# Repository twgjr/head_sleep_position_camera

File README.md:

# Tracking head position while sleeping
In 2017 my new born son had formed a flat spot on his head due to Torticollis (stiff neck that makes it hard or painful to turn your head).  Fortunately, he had successful physical therapy to correct the condition.

That inspired this hobby project as a way to track how long an infant spent sleeping on one part of their head.  At the time (2017) I was a power system engineer for electric utilities.  I had learned some embedded system PCB designand programming in school, but was a little rusty.  It allowed me to explore embedded PCB design and programming and also introduced me to machine learning and AI applications.

As a result of Git not yet being serious part of my life in 2017, very few files were saved other than mentioned below.  I have since then adopted Git to save progress with my software and hardware projects!

## Development
I expermented on two different device concepts:  

1.  Wearable:  A battery powered tile worn as a head band.  It used an accelerometer to track the position of the head.  Though simple and inexpensive, this was quickly abandoned due to risks of choking and batteries near infants.

1.  Camera:  Camera to observe sleeping head pose without contact.  Used head pose detection AI and on-board accelerometer to estimate the head position relative to a flat level bed.  Two approaches were tried for the camera:

    * On-device AI model:  The camera used a Raspberry Pi to run a head pose detection AI model.  The head pose would then be corrected with the accelerometer data to estimate the head position relative to the bed.  I based the proof of concept on the LearnOpenCV blog post [Head Pose Estimation using OpenCV and Dlib](https://www.learnopencv.com/head-pose-estimation-using-opencv-and-dlib/).  This could only process 1 frame per 30 seconds. So, I would need to find a more efficient AI model or a more powerful (expensive) processor.

    * Cloud AI model:  The camera would send an image of the head to AWS Rekognition to calculate the head pose relative to the camera.  The head pose would then be corrected with the accelerometer data to estimate the head position relative to the bed.  This was the most promising approach, and least expensive hardware.  However, the cost of running the AI model on the cloud was too expensive to be practical.  The PCB I designed for this approach is the only work I have saved.  It is in the `hardware` directory.  (requires Fusion 360 to view or edit.)

## Current Status and Future Work
The cost of running the AI to track the head position was too cost prohibitive to be practical for most people at the time.  It would either require a lot of cloud computing resources or much more expensive processing on the device itself.

I have since moved on to other projects, but I would like to revisit this project in the future.  When I do, I would like to explore the following:
*  More efficient AI models (computer vision and machine learning have advanced a lot since 2017)
*  More efficient processing on the device (newer processors with AI acceleration)

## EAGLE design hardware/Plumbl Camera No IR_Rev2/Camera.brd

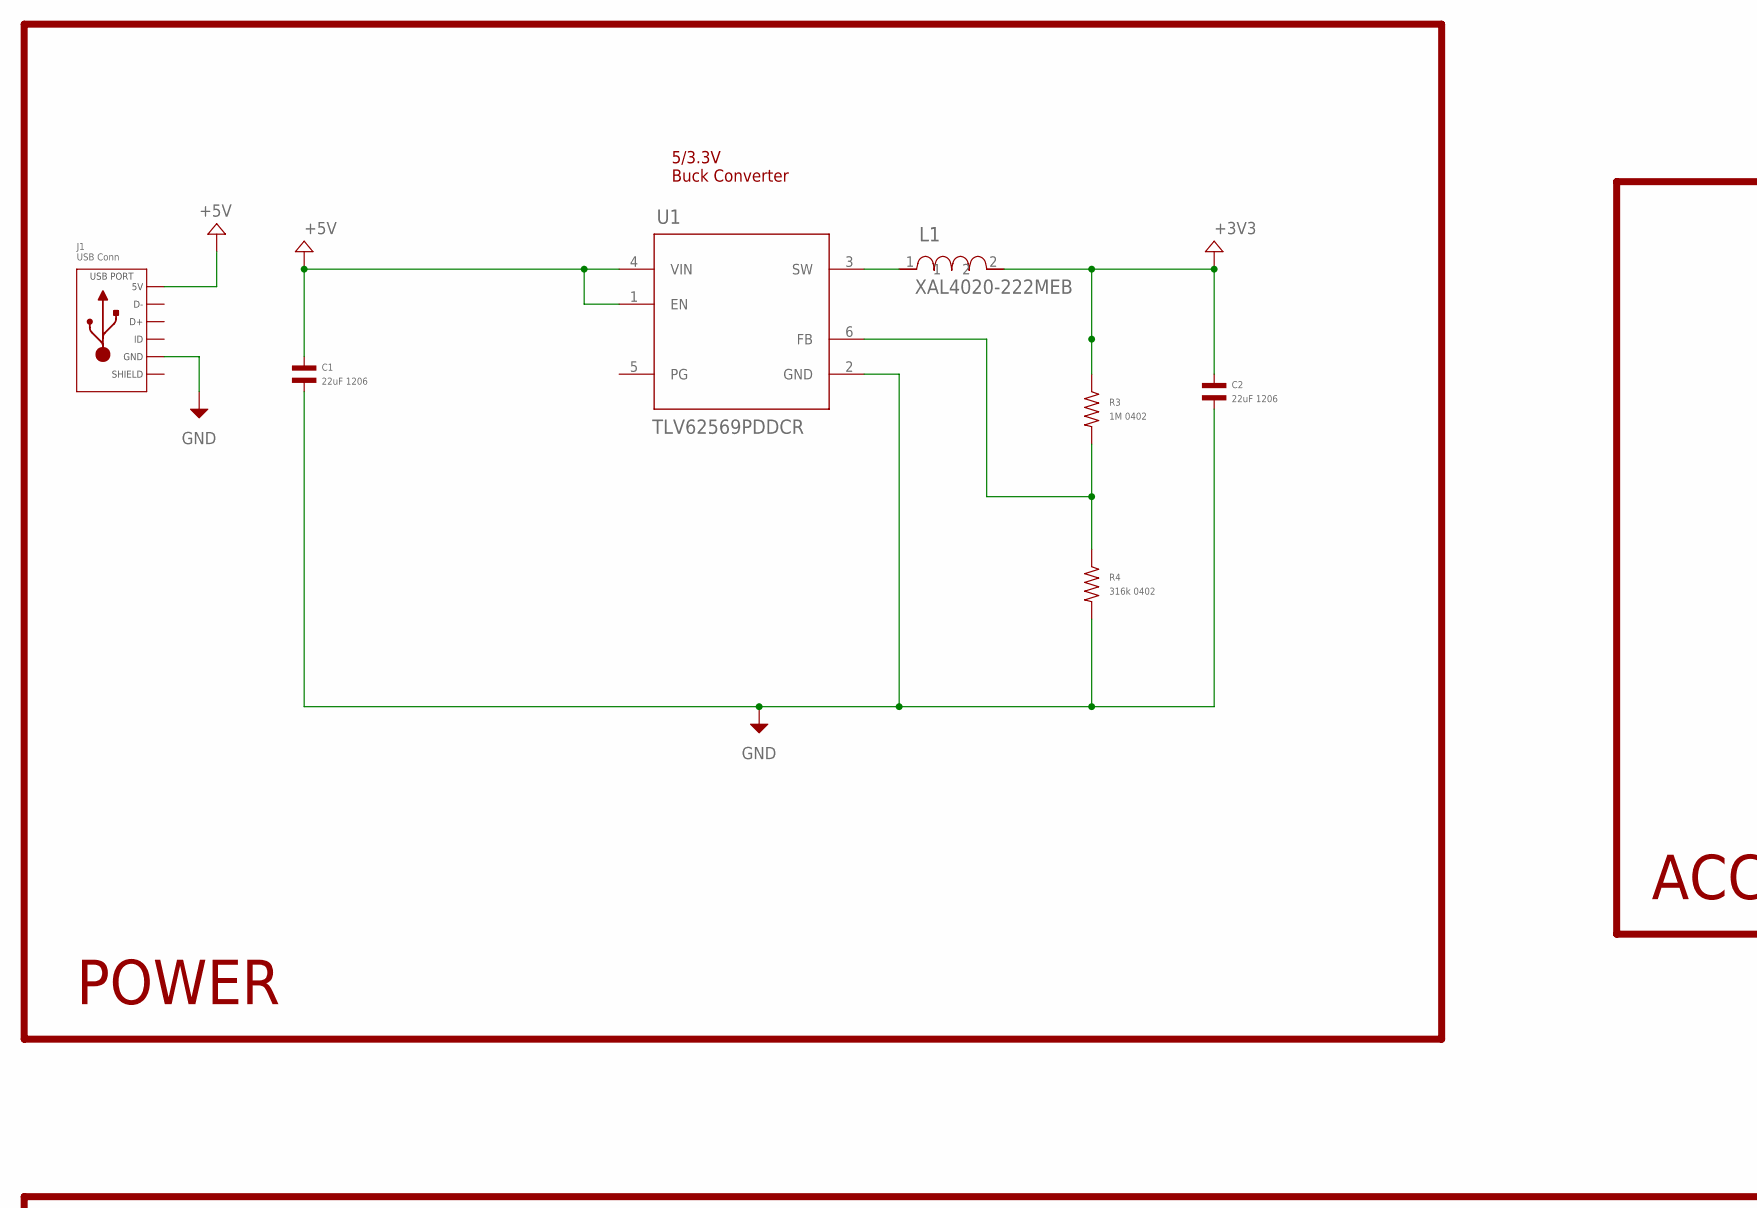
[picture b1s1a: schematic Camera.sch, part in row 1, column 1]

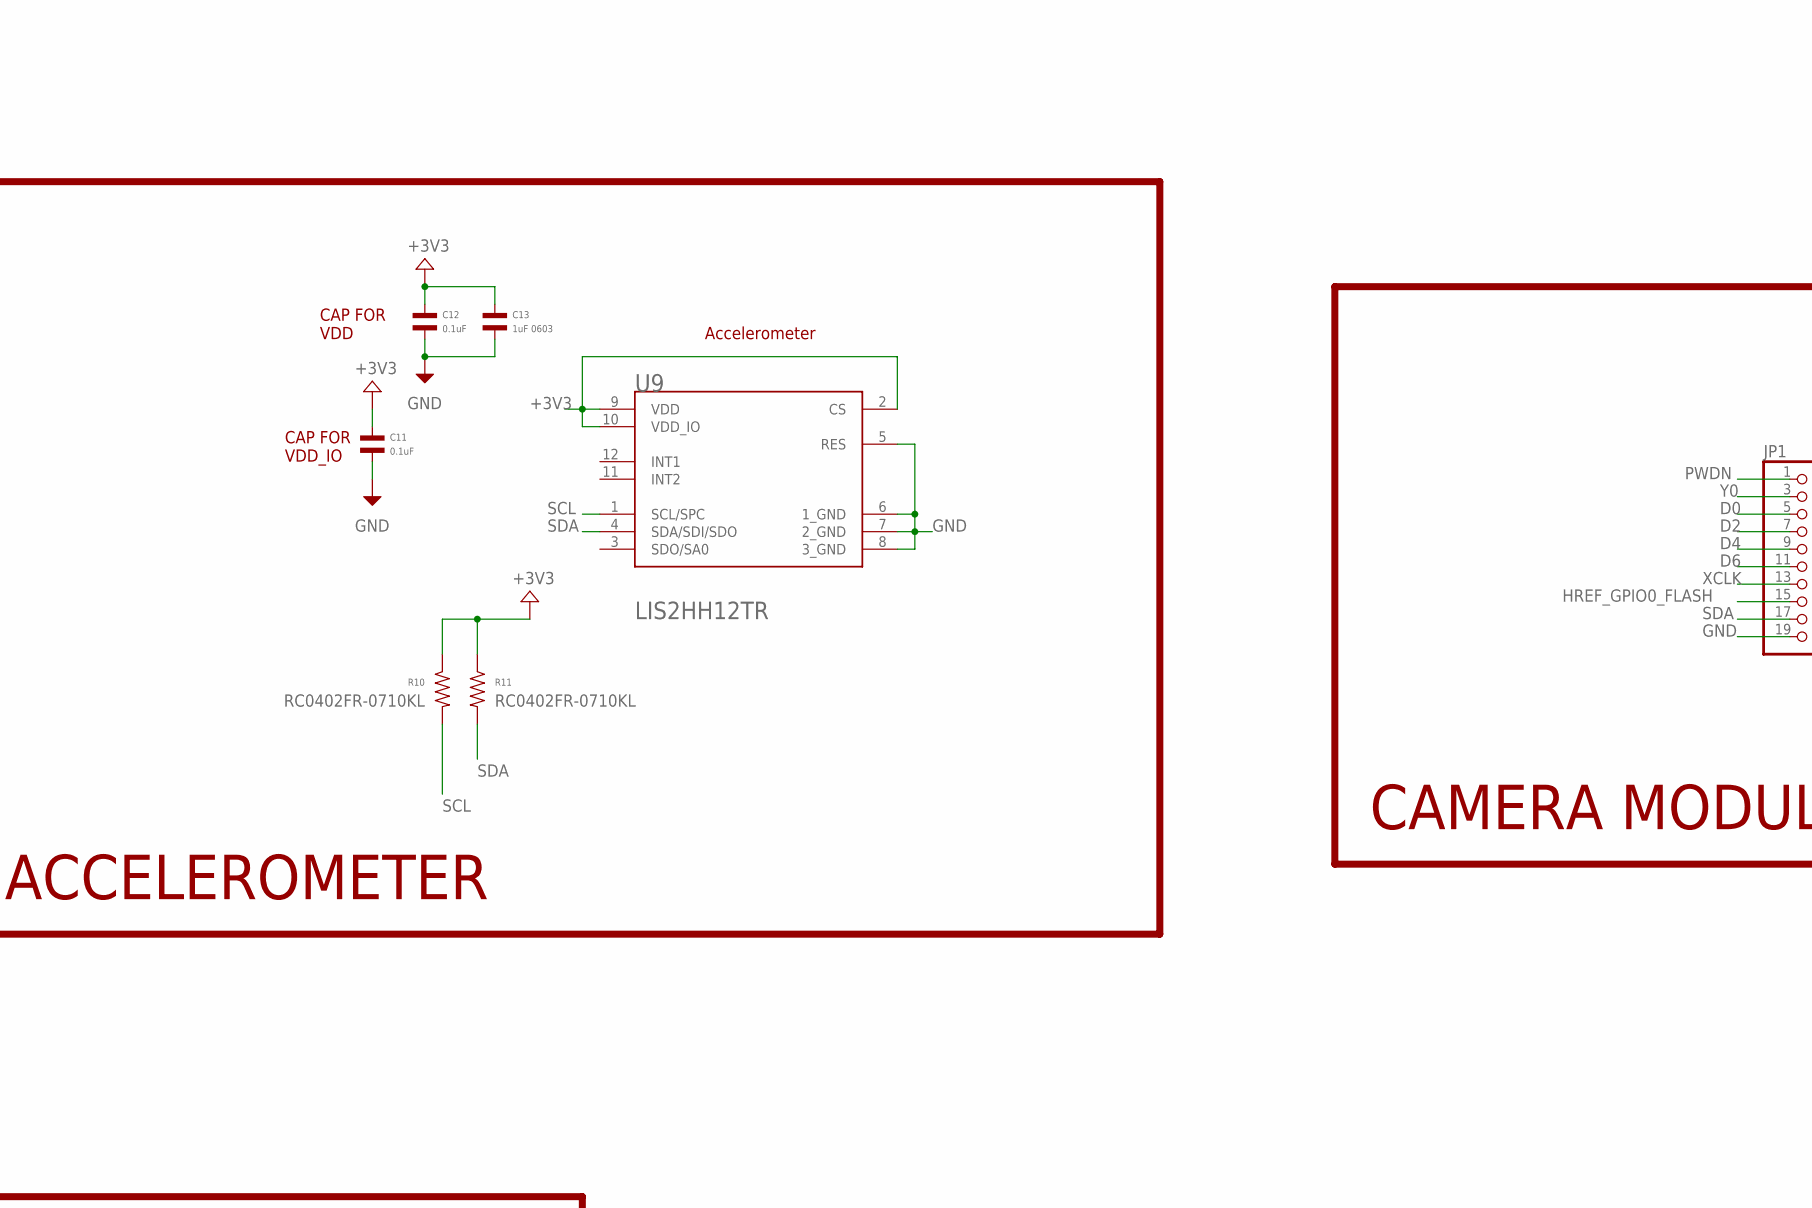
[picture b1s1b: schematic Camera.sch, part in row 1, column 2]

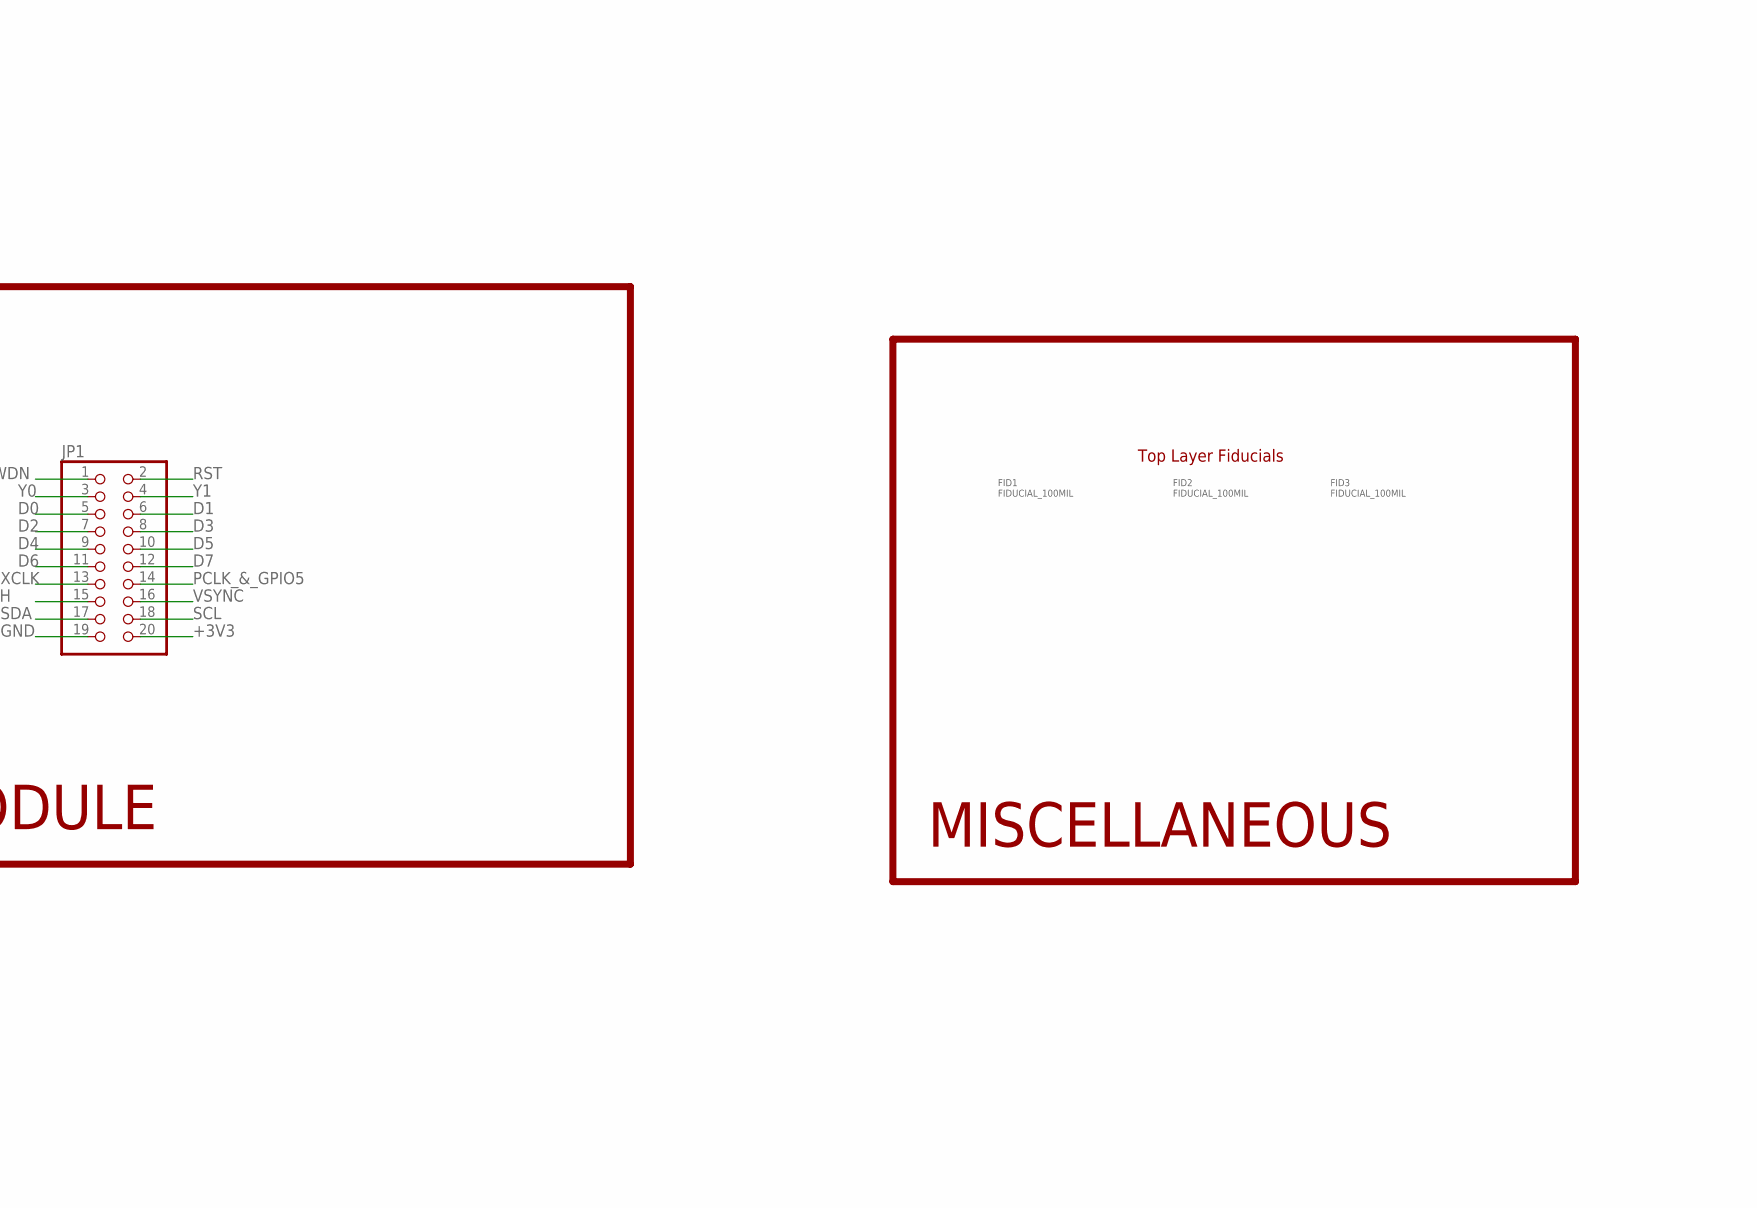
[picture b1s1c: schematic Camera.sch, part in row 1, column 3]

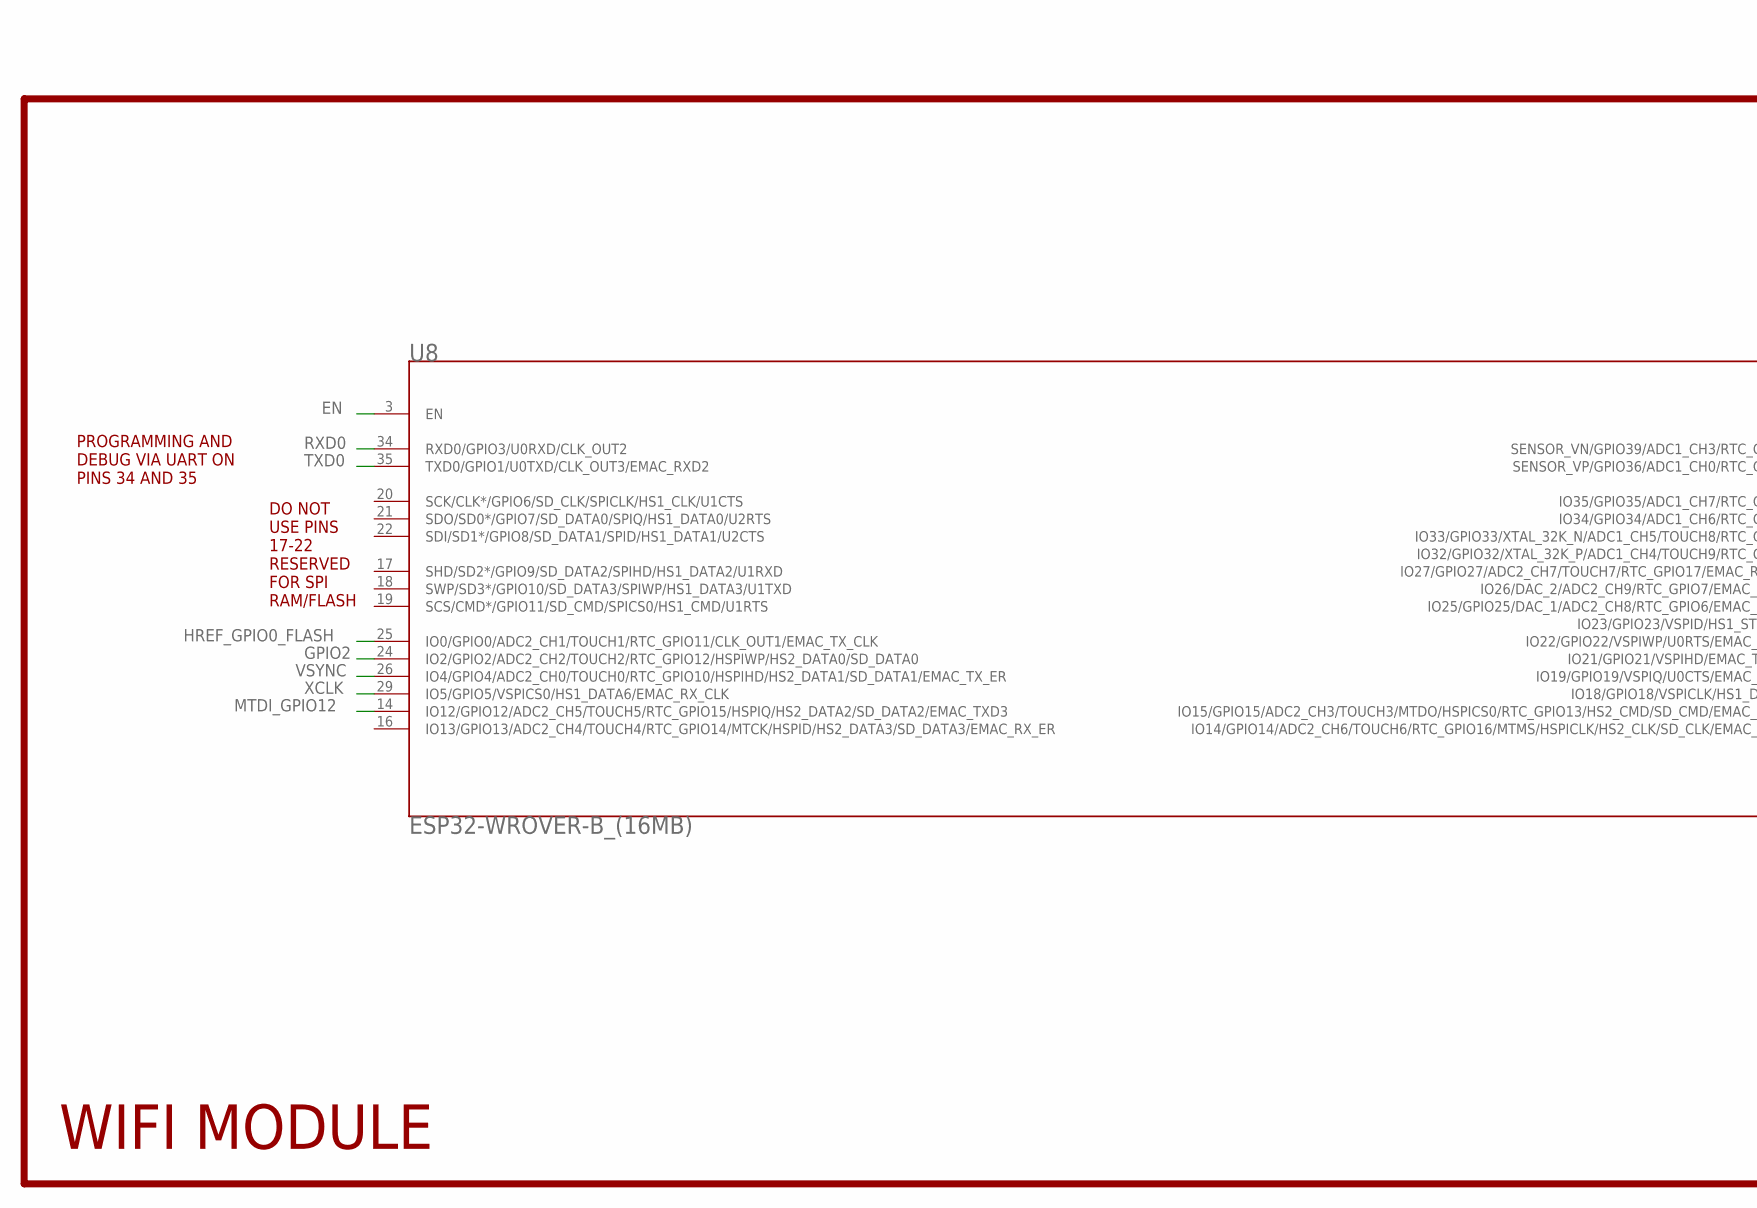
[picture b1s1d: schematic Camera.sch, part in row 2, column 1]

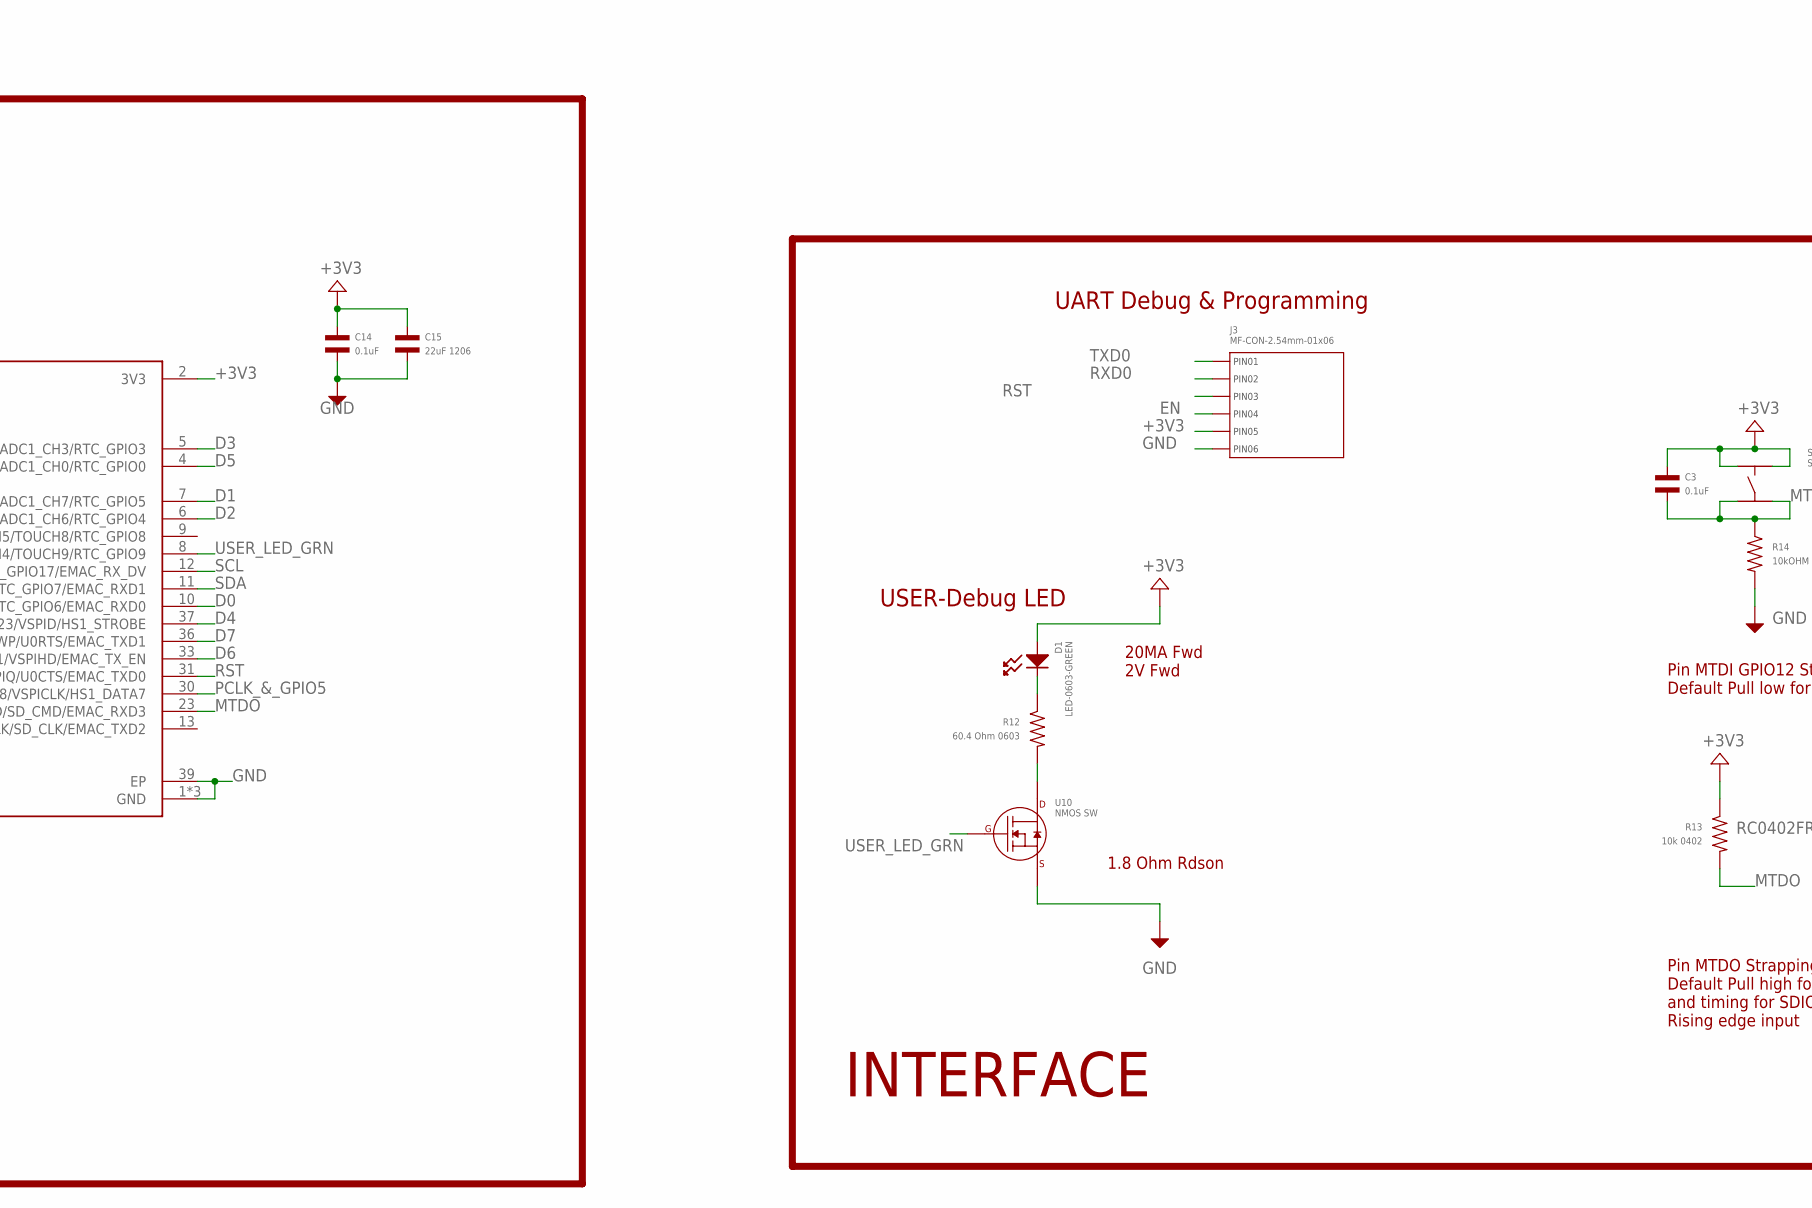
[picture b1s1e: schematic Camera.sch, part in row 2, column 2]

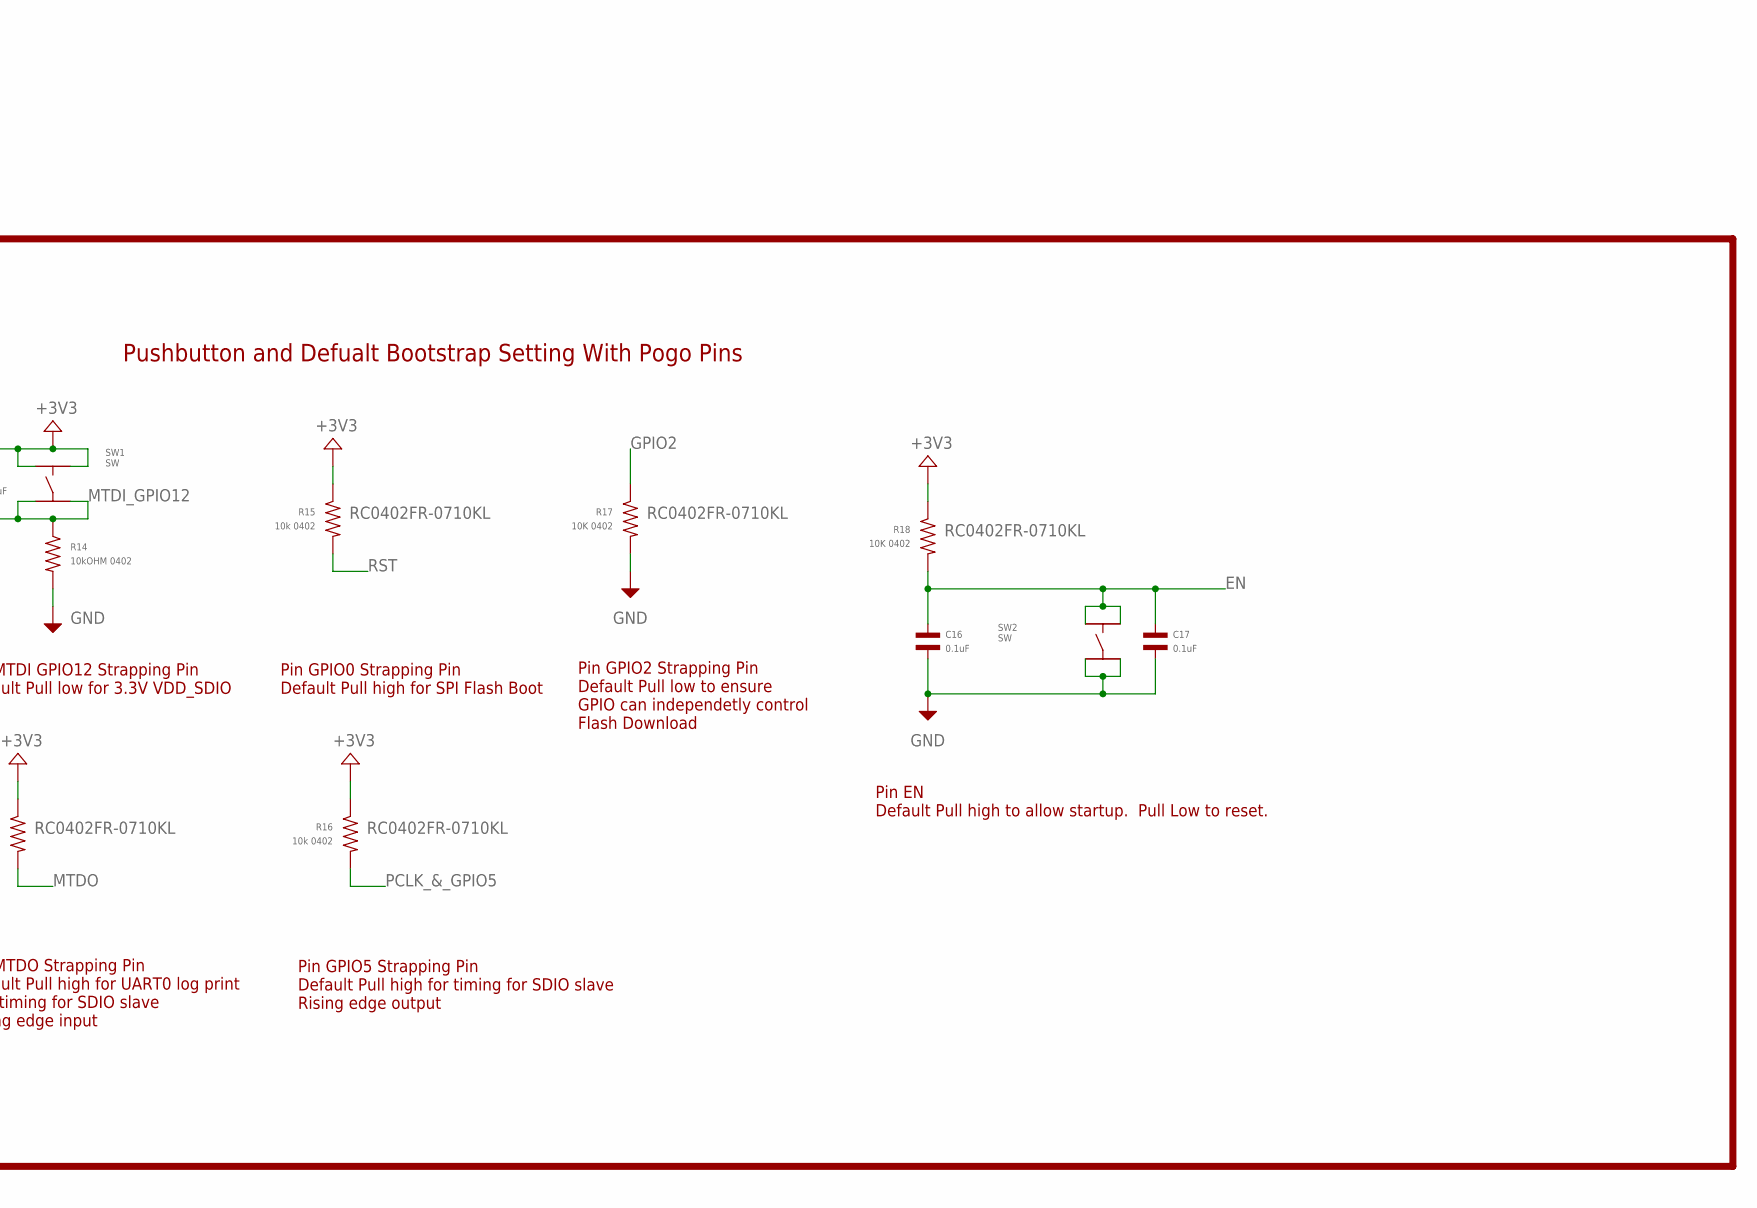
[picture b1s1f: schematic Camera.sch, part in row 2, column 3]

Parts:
C1, C2, C15: 22uF 1206; C1206; MPN CL31A226KPHNNNE
C3, C11, C12, C14, C16, C17: 0.1uF; C0402; MPN CL05B104KO5NNNC
C13: 1uF 0603; C0603; MPN CL05A105KO5NNNC
D1: LED-0603-GREEN; LED0603; MPN LTST-C190KGKT
FID1, FID2, FID3: FIDUCIAL_100MIL
J1: USB Conn; MICROUSB-RIGHT; MPN 10118193-0001LF
J3: MF-CON-2.54mm-01x06; PTH_2.54MM_01X06
JP1: PINHD-2X10; 2X10
L1: XAL4020-222MEB; XAL4020
R3: 1M 0402; R0402; MPN RC0402FR-071ML
R4: 316k 0402; R0402; TOLERANCE 1%; MPN RC0402FR-07316KL
R10, R11: RESISTOR_0402; R0402; MPN RC0402FR-0710KL
R12: 60.4 Ohm 0603; R0603; MPN RC0603FR-0760R4L
R13, R15, R16: 10k 0402; R0402; MPN RC0402FR-0710KL
R14: 10kOHM 0402; R0402; MPN RC0402FR-0710KL
R17, R18: 10K 0402; R0402; MPN RC0402FR-0710KL
SW1, SW2: SW; TACT6MM; MPN PTS645SM43SMTR92 LFS
U1: TLV62569PDDCR; DDC0006A
U8: ESP32-WROVER-B_(16MB); XCVR_ESP32-WROVER-B_(16MB)
U9: ST_MICROELECTRONICS_LIS2HH12TRST_MICROELECTRONICS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; ST_MICROELECTRONICS_LIS2HH12TR_0
U10: NMOS SW; SOT-23-3; MPN BSS138

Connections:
+3V3: C2.P$1, C3.P$1, C11.P$1, C12.P$1, C13.P$1, C14.P$1, C15.P$1, D1.ANODE, J3.P$5 (PIN5), JP1.20, L1.2, R3.P$1, R10.P$1, R11.P$1, R13.P$1, R15.P$1, R16.P$1, R18.P$1, SW1.P$1, SW1.P$2, U8.2 (3V3), U9.2 (CS), U9.9 (VDD), U9.10 (VDD_IO)
+5V: C1.P$1, J1.1 (5V), U1.1 (EN), U1.4 (VIN)
D0: JP1.5, U8.10 (IO25/GPIO25/DAC_1/ADC2_CH8/RTC_GPIO6/EM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)
D1: JP1.6, U8.7 (IO35/GPIO35/ADC1_CH7/RTC_GPIO5)
D2: JP1.7, U8.6 (IO34/GPIO34/ADC1_CH6/RTC_GPIO4)
D3: JP1.8, U8.5 (SENSOR_VN/GPIO39/ADC1_CH3/RTC_GPIO3)
D4: JP1.9, U8.37 (IO23/GPIO23/VSPID/HS1_STROBE)
D5: JP1.10, U8.4 (SENSOR_VP/GPIO36/ADC1_CH0/RTC_GPIO0)
D6: JP1.11, U8.33 (IO21/GPIO21/VSPIHD/EMAC_TX_EN)
D7: JP1.12, U8.36 (IO22/GPIO22/VSPIWP/U0RTS/EMAC_TXD1)
EN: C16.P$1, C17.P$1, J3.P$4 (PIN4), R18.P$2, SW2.P$1, SW2.P$2, U8.3 (EN)
GND: C1.P$2, C2.P$2, C11.P$2, C12.P$2, C13.P$2, C14.P$2, C15.P$2, C16.P$2, C17.P$2, J1.5 (GND), J3.P$6 (PIN6), JP1.19, R4.P$2, R14.P$2, R17.P$2, SW2.P$3, SW2.P$4, U1.2 (GND), U8.1 (GND), U8.15 (GND), U8.38 (GND), U8.39 (EP), U9.5 (RES), U9.6 (1_GND), U9.7 (2_GND), U9.8 (3_GND), U10.P$2 (SOURCE)
GPIO2: R17.P$1, U8.24 (IO2/GPIO2/ADC2_CH2/TOUCH2/RTC_GPIO12/HS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)
HREF_GPIO0_FLASH: JP1.15, U8.25 (IO0/GPIO0/ADC2_CH1/TOUCH1/RTC_GPIO11/CL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)
MTDI_GPIO12: C3.P$2, R14.P$1, SW1.P$3, SW1.P$4, U8.14 (IO12/GPIO12/ADC2_CH5/TOUCH5/RTC_GPIO15/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)
MTDO: R13.P$2, U8.23 (IO15/GPIO15/ADC2_CH3/TOUCH3/MTDO/HSPICS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)
unnamed: L1.1, U1.3 (SW)
unnamed: R3.P$2, R4.P$1, U1.6 (FB)
unnamed: D1.CATHODE, R12.P$1
unnamed: R12.P$2, U10.P$3 (DRAIN)
PCLK_&_GPIO5: JP1.14, R16.P$2, U8.30 (IO18/GPIO18/VSPICLK/HS1_DATA7)
PWDN: JP1.1
RST: J3.P$3 (PIN3), JP1.2, R15.P$2, U8.31 (IO19/GPIO19/VSPIQ/U0CTS/EMAC_TXD0)
RXD0: J3.P$2 (PIN2), U8.34 (RXD0/GPIO3/U0RXD/CLK_OUT2)
SCL: JP1.18, R10.P$2, U8.12 (IO27/GPIO27/ADC2_CH7/TOUCH7/RTC_GPIO17/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), U9.1 (SCL/SPC)
SDA: JP1.17, R11.P$2, U8.11 (IO26/DAC_2/ADC2_CH9/RTC_GPIO7/EMAC_RXD1), U9.4 (SDA/SDI/SDO)
SLD: J1.S1 (SLD), J1.S2 (SLD), J1.S3 (SLD), J1.S4 (SLD), J1.S5 (SLD), J1.S6 (SLD)
TXD0: J3.P$1 (PIN1), U8.35 (TXD0/GPIO1/U0TXD/CLK_OUT3/EMAC_RXD2)
USER_LED_GRN: U8.8 (IO32/GPIO32/XTAL_32K_P/ADC1_CH4/TOUCH9/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), U10.P$1 (GATE)
VSYNC: JP1.16, U8.26 (IO4/GPIO4/ADC2_CH0/TOUCH0/RTC_GPIO10/HS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)
XCLK: JP1.13, U8.29 (IO5/GPIO5/VSPICS0/HS1_DATA6/EMAC_RX_CLK)
Y0: JP1.3
Y1: JP1.4

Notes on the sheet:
CAMERA MODULE
POWER
ACCELEROMETER
WIFI MODULE
Accelerometer
5/3.3V Buck Converter
INTERFACE
DO NOT USE PINS 17-22 RESERVED FOR SPI RAM/FLASH
PROGRAMMING AND DEBUG VIA UART ON PINS 34 AND 35
CAP FOR VDD_IO
CAP FOR VDD
UART Debug & Programming
USER-Debug LED
Pushbutton and Defualt Bootstrap Setting With Pogo Pins
20MA Fwd 2V Fwd
1.8 Ohm Rdson
Pin MTDI GPIO12 Strapping Pin Default Pull low for 3.3V VDD_SDIO
Pin GPIO0 Strapping Pin Default Pull high for SPI Flash Boot
Pin GPIO2 Strapping Pin Default Pull low to ensure GPIO can independetly control Flash Download
Pin MTDO Strapping Pin Default Pull high for UART0 log print and timing for SDIO slave Rising edge input
Pin GPIO5 Strapping Pin Default Pull high for timing for SDIO slave Rising edge output
MISCELLANEOUS
Top Layer Fiducials
Pin EN Default Pull high to allow startup. Pull Low to reset.

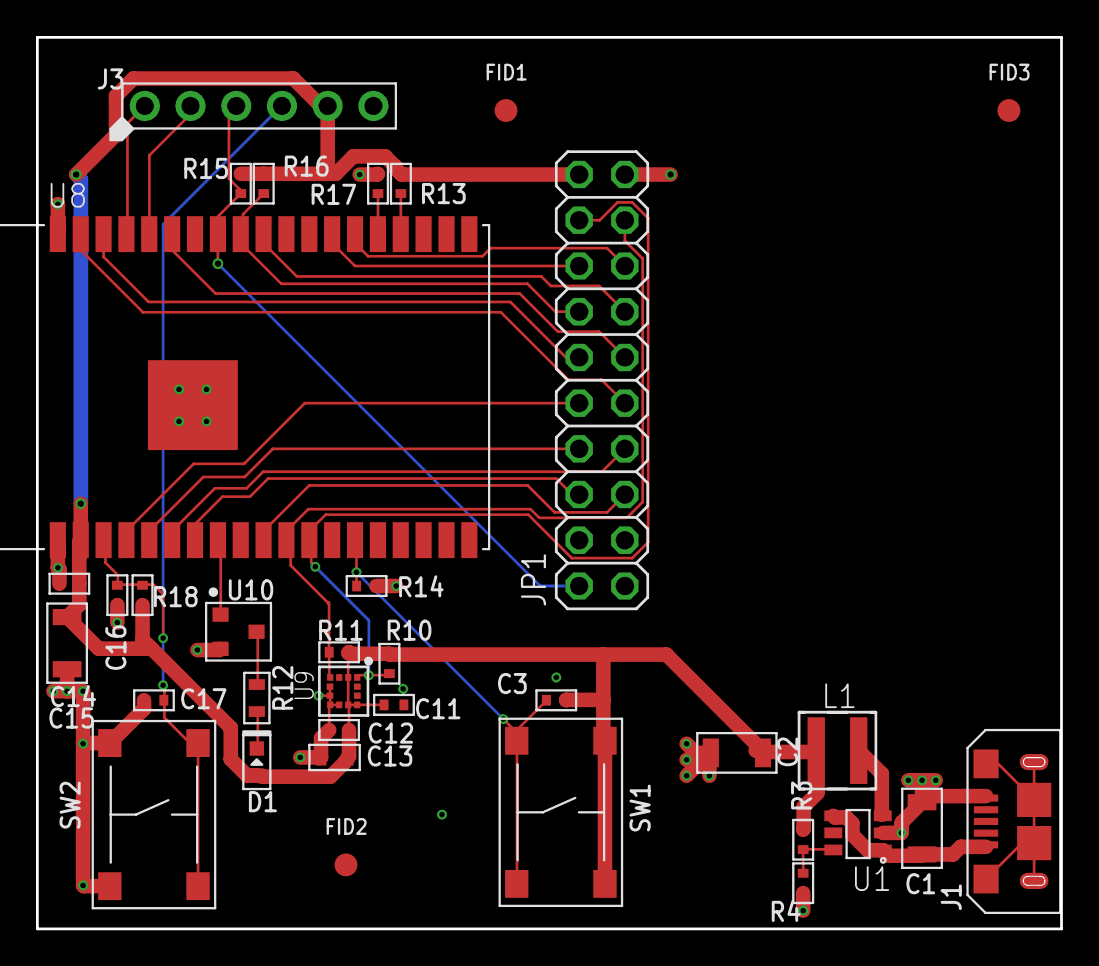
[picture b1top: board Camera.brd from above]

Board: 2 copper layers, 56.9 x 49.5 mm, 35 parts (0 on the bottom side), 30 nets.

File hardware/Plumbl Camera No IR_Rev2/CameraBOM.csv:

Part,Value,Device,Package,Description,AVAILABILITY,CENTROID_NOT_SPECIFIED,DATASHEET,DATASHEETURL,DCR,DESCRIPTION,DIELECTRIC,DIGIKEY_DESCRIPTION,DIGIKEY_PART_NUMBER,HOUSEPART,IDC,L,LABEL01,LABEL02,LABEL03,LABEL04,LABEL05,LABEL06,LAND_PATTERN,LEAD_FREE,MANUFACTURER,MANUFACTURER_NAME,MANUFACTURER_PART_NUMBER,MF,MOUSER_PART_NUMBER,MPN,PACKAGE,PARTNUMBER,POPULATE,PREFIX,PRICE,REFDES,ROHS,TEMPERATURE_RANGE_HIGH,TEMPERATURE_RANGE_LOW,TOLERANCE,TYPE,URL,VALUE,VENDOR,VOLTAGE,WATTAGE
C1,22uF 1206,CAPACITOR_NP_1206,C1206,Library:  MF_Passives,,,,,,,,,,NO,,,,,,,,,,,,,,,,CL31A226KPHNNNE,,,1,,,,,,,,,,,,,
C2,22uF 1206,CAPACITOR_NP_1206,C1206,Library:  MF_Passives,,,,,,,,,,YES,,,,,,,,,,,,,,,,CL31A226KPHNNNE,,,1,,,,,,,,,,,,,
C3,0.1uF,CAPACITOR_NP_0402,C0402,Library:  MF_Passives,,,,,,,,,,NO,,,,,,,,,,,,,,,,CL05B104KO5NNNC,,,1,,,,,,,,,,,,,
C11,0.1uF,CAPACITOR_NP_0402,C0402,Library:  MF_Passives,,,,,,,,,,No,,,,,,,,,,,,,,,,CL05B104KO5NNNC,,,1,,,,,,,,,,,,,
C12,0.1uF,CAPACITOR_NP_0402,C0402,Library:  MF_Passives,,,,,,,,,,NO,,,,,,,,,,,,,,,,CL05B104KO5NNNC,,,1,,,,,,,,,,,,,
C13,1uF 0603,CAPACITOR_NP_0603,C0603,Library:  MF_Passives,,,,,,,,,,NO,,,,,,,,,,,,,,,,CL05A105KO5NNNC,,,1,,,,,,,,,,,,,
C14,0.1uF,CAPACITOR_NP_0402,C0402,Library:  MF_Passives,,,,,,,,,,NO,,,,,,,,,,,,,,,,CL05B104KO5NNNC,,,1,,,,,,,,,,,,,
C15,22uF 1206,CAPACITOR_NP_1206,C1206,Library:  MF_Passives,,,,,,,,,,YES,,,,,,,,,,,,,,,,CL31A226KPHNNNE,,,1,,,,,,,,,,,,,
C16,0.1uF,CAPACITOR_NP_0402,C0402,Library:  MF_Passives,,,,,,,,,,NO,,,,,,,,,,,,,,,,CL05B104KO5NNNC,,,1,,,,,,,,,,,,,
C17,0.1uF,CAPACITOR_NP_0402,C0402,Library:  MF_Passives,,,,,,,,,,NO,,,,,,,,,,,,,,,,CL05B104KO5NNNC,,,1,,,,,,,,,,,,,
D1,LED-0603-GREEN,LED_SINGLE-0603-GREEN,LED0603,Library:  MF_LEDs,,,,,,,,,,NO,,,,,,,,,,,,,,,,LTST-C190KGKT,,,1,,,,,,,,,,MF-LED-0603-GREEN,,,
FID1,FIDUCIAL_100MIL,FIDUCIAL_100MIL,FIDUCIAL_100MIL,Library:  MF_Aesthetics,,,,,,,,,,NO,,,,,,,,,,,,,,,,,,,0,,,,,,,,,,,,,
FID2,FIDUCIAL_100MIL,FIDUCIAL_100MIL,FIDUCIAL_100MIL,Library:  MF_Aesthetics,,,,,,,,,,NO,,,,,,,,,,,,,,,,,,,0,,,,,,,,,,,,,
FID3,FIDUCIAL_100MIL,FIDUCIAL_100MIL,FIDUCIAL_100MIL,Library:  MF_Aesthetics,,,,,,,,,,NO,,,,,,,,,,,,,,,,,,,0,,,,,,,,,,,,,
J1,USB Conn,USB_MICRO_RIGHT,MICROUSB-RIGHT,Library:  MF_Connectors,,,,,,,,,,NO,,,,,,,,,,,,,,,,10118193-0001LF,,,1,,,,,,,,,,MF-CON-MICROUSB-RIGHT,,,
J3,MF-CON-2.54mm-01x06,CON_01X06_PTH_2.54MM,PTH_2.54MM_01X06,Library:  MF_Connectors,,,,,,,,,,YES,,,,,,,,,,,,,,,,MF-CON-2.54mm-01x06,,,1,,,,,,,,,https://factory.macrofab.com/part/MF-CON-2.54mm-01x06,MF-CON-2.54mm-01x06,,,
JP1,,PINHD-2X10,2X10,PIN HEADER,,,,,,,,,,,,,,,,,,,,,,,,,,,,,,,,,,,,,,,,,,
L1,XAL4020-222MEB,XAL4020-222MEB,XAL4020,,,,,httpwww.coilcraft.compdfsxal4000.pdf,0.0352,,,,,,5.5,2.20E+06,,,,,,,,,,Coilcraft,XAL4020222MEB,,,,,,,,,,,,,,,,,Coilcraft,,
R3,1M 0402,RESISTOR_0402,R0402,Library:  MF_Passives,,,,,,,,,,,,,,,,,,,,,,,,,,RC0402FR-071ML,,,1,,,,,,,,,,,,,
R4,316k 0402,RESISTOR_0402,R0402,Library:  MF_Passives,,,,,,,,,,,,,,,,,,,,,,,,,,RC0402FR-07316KL,,,1,,,,,,,1%,,,,,,
R10,,RESISTOR_0402,R0402,Library:  MF_Passives,,,,,,,,,,NO,,,,,,,,,,,,,,,,RC0402FR-0710KL,,,1,,,,,,,,,,,,,
R11,,RESISTOR_0402,R0402,Library:  MF_Passives,,,,,,,,,,NO,,,,,,,,,,,,,,,,RC0402FR-0710KL,,,1,,,,,,,,,,,,,
R12,60.4 Ohm 0603,RESISTOR_0603,R0603,Library:  MF_Passives,,,,,,,,,,,,,,,,,,,,,,,,,,RC0603FR-0760R4L,,,1,,,,,,,,,,,,,
R13,10k 0402,RESISTOR_0402,R0402,Library:  MF_Passives,,,,,,,,,,NO,,,,,,,,,,,,,,,,RC0402FR-0710KL,,,1,,,,,,,,,,,,,
R14,10kOHM 0402,RESISTOR_0402,R0402,Library:  MF_Passives,,,,,,,,,,NO,,,,,,,,,,,,,,,,RC0402FR-0710KL,,,1,,,,,,,,,,,,,
R15,10k 0402,RESISTOR_0402,R0402,Library:  MF_Passives,,,,,,,,,,NO,,,,,,,,,,,,,,,,RC0402FR-0710KL,,,1,,,,,,,,,,,,,
R16,10k 0402,RESISTOR_0402,R0402,Library:  MF_Passives,,,,,,,,,,NO,,,,,,,,,,,,,,,,RC0402FR-0710KL,,,1,,,,,,,,,,,,,
R17,10K 0402,RESISTOR_0402,R0402,Library:  MF_Passives,,,,,,,,,,NO,,,,,,,,,,,,,,,,RC0402FR-0710KL,,,1,,,,,,,,,,,,,
R18,10K 0402,RESISTOR_0402,R0402,Library:  MF_Passives,,,,,,,,,,NO,,,,,,,,,,,,,,,,RC0402FR-0710KL,,,1,,,,,,,,,,,,,
SW1,SW,TACT_6MM,TACT6MM,Library:  MF_Switches,,,,,,,,,,NO,,,,,,,,,,,,,,,,PTS645SM43SMTR92 LFS,,,1,,,,,,,,,https://factory.macrofab.com/part/MF-SW-TACT-6MM,MF-SW-TACT-6MM,,,
SW2,SW,TACT_6MM,TACT6MM,Library:  MF_Switches,,,,,,,,,,NO,,,,,,,,,,,,,,,,PTS645SM43SMTR92 LFS,,,1,,,,,,,,,https://factory.macrofab.com/part/MF-SW-TACT-6MM,MF-SW-TACT-6MM,,,
U1,TLV62569PDDCR,TLV62569PDDCR,DDC0006A,,,,,,,,,,,,,,,,,,,,,,Texas Instruments,Texas Instruments,,,,TLV62569PDDCR,,TLV62569PDDC,1,,,RefDes,,,,,TYPE,,TLV62569PDDCR,,,
U8,ESP32-WROVER-B_(16MB),ESP32-WROVER-B_(16MB),XCVR_ESP32-WROVER-B_(16MB),WiFi SMD Module,,,,,,,,,,,,,,,,,,,,,,,,,,,,,,,,,,,,,,,,,,
U9,ST_MICROELECTRONICS_LIS2HH12TRST_MICROELECTRONICS_LIS2HH12TR_0_0,ST_MICROELECTRONICS_LIS2HH12TRST_MICROELECTRONICS_LIS2HH12TR_0_0,ST_MICROELECTRONICS_LIS2HH12TR_0,ACCELEROMETER 2-8G I2C/SPI 12LGA,,No,http://www2.st.com/content/ccc/resource/technical/document/d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,,,,,IC ACCELEROMETER 2-8G I2C/SPI 12LGA,497-15069-1-ND,,,,,,,,,,http://www.st.com/content/ccc/resource/technical/document/te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,yes,,,,ST Microelectronics,511-LIS2HH12TR,LIS2HH12TR,VFLGA12,,1,U,,,yes,+85°C,-40°C,,,,,,,
U10,NMOS SW,N-CHANNEL_FET_BSS138_SOT-23-3,SOT-23-3,Library:  MF_Discrete_Semiconductor,,,,,,,,,,NO,,,,,,,,,,,,,,,,BSS138,,,1,,,,,,,,,,MF-DSC-SOT233-BSS138,,,
